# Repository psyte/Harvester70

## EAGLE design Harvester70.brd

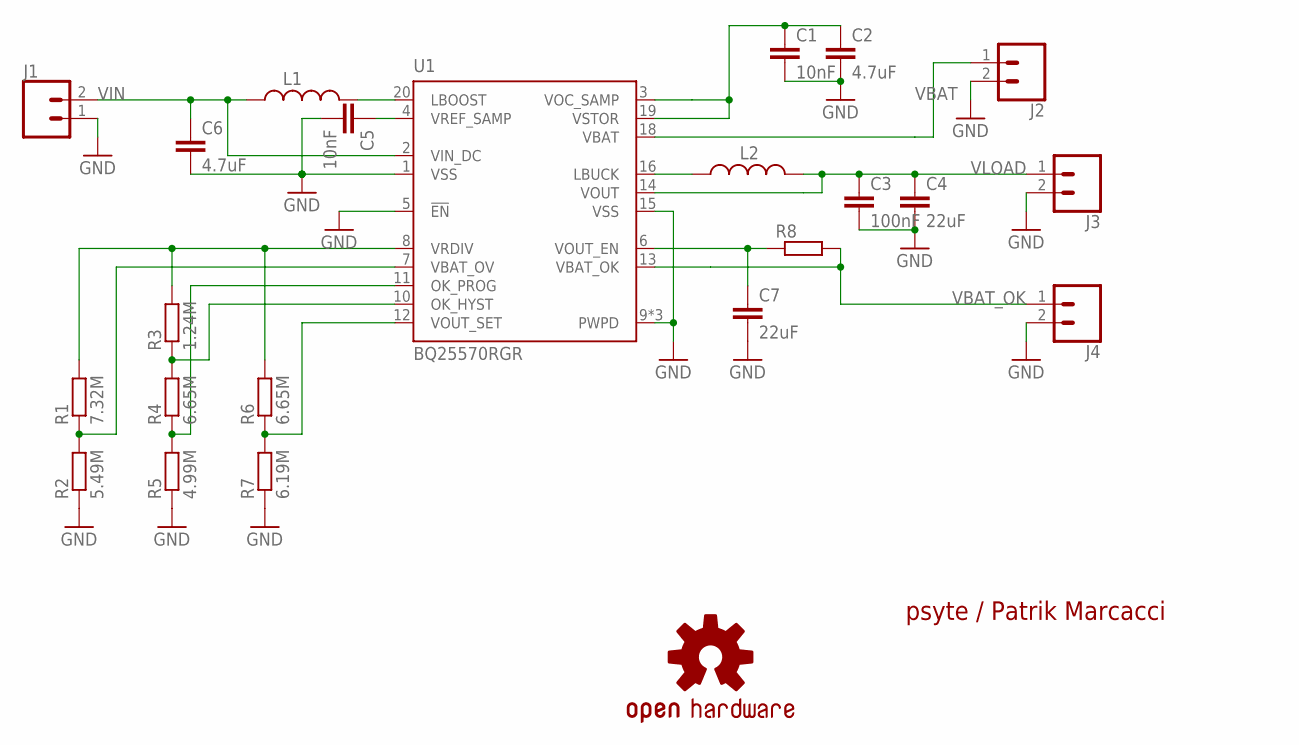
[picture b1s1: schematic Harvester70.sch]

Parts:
C1, C5: 10nF; C0603K
C2, C6: 4.7uF; C0603K
C3: 100nF; C0603K
C4, C7: 22uF; C0603K
J1, J2, J3, J4: CONN_02; 1X02
L1: LPS4018-223M; LPS4018
L2: LPS4018-103M; LPS4018
LOGO2: OSHW-LOGOS; OSHW-LOGO-S
R1: 7.32M; R0603
R2: 5.49M; R0603
R3: 1.24M; R0603
R4, R6: 6.65M; R0603
R5: 4.99M; R0603
R7: 6.19M; R0603
R8: R-EU_R0603; R0603
U1: BQ25570RGR; RGR_S-PVQFN-N20

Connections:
GND: C1.2, C2.2, C3.2, C4.2, C5.2, C6.2, C7.2, J1.1, J2.2, J3.2, J4.2, R2.1, R5.1, R7.1, U1.1 (VSS), U1.5 (!EN), U1.9 (PWPD), U1.15 (VSS), U1.17 (PWPD), U1.EXP (PWPD)
unnamed: R1.1, R2.2, U1.7 (VBAT_OV)
unnamed: R4.1, R5.2, U1.11 (OK_PROG)
unnamed: R3.1, R4.2, U1.10 (OK_HYST)
unnamed: R6.1, R7.2, U1.12 (VOUT_SET)
unnamed: C1.1, C2.1, U1.3 (VOC_SAMP), U1.19 (VSTOR)
unnamed: C7.1, R8.1, U1.6 (VOUT_EN)
unnamed: L2.1, U1.16 (LBUCK)
unnamed: L1.2, U1.20 (LBOOST)
unnamed: C5.1, U1.4 (VREF_SAMP)
VBAT: J2.1, U1.18 (VBAT)
VBAT_OK: J4.1, R8.2, U1.13 (VBAT_OK)
VIN: C6.1, J1.2, L1.1, U1.2 (VIN_DC)
VLOAD: C3.1, C4.1, J3.1, L2.2, U1.14 (VOUT)
VRDIV: R1.2, R3.2, R6.2, U1.8 (VRDIV)

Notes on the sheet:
psyte / Patrik Marcacci

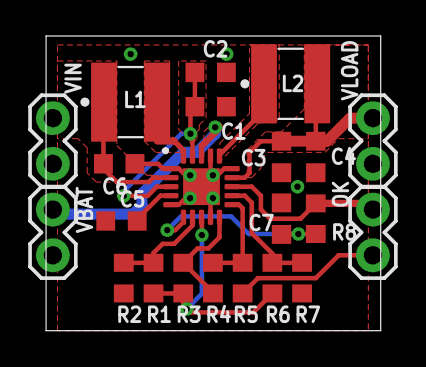
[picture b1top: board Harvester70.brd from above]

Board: 2 copper layers, 18.6 x 16.4 mm, 23 parts (1 on the bottom side), 15 nets.

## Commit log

2019-05-08 First
2019-05-22 Added gerbers and resistor values

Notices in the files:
parts and their libraries:
energy-harvesting-pmic: Creative Commons Attribution-ShareAlike 4.0 International
SparkFun-Connectors: Licensing: Creative Commons ShareAlike 4.0 International - https://creativecommons.org/licenses/by-sa/4.0
